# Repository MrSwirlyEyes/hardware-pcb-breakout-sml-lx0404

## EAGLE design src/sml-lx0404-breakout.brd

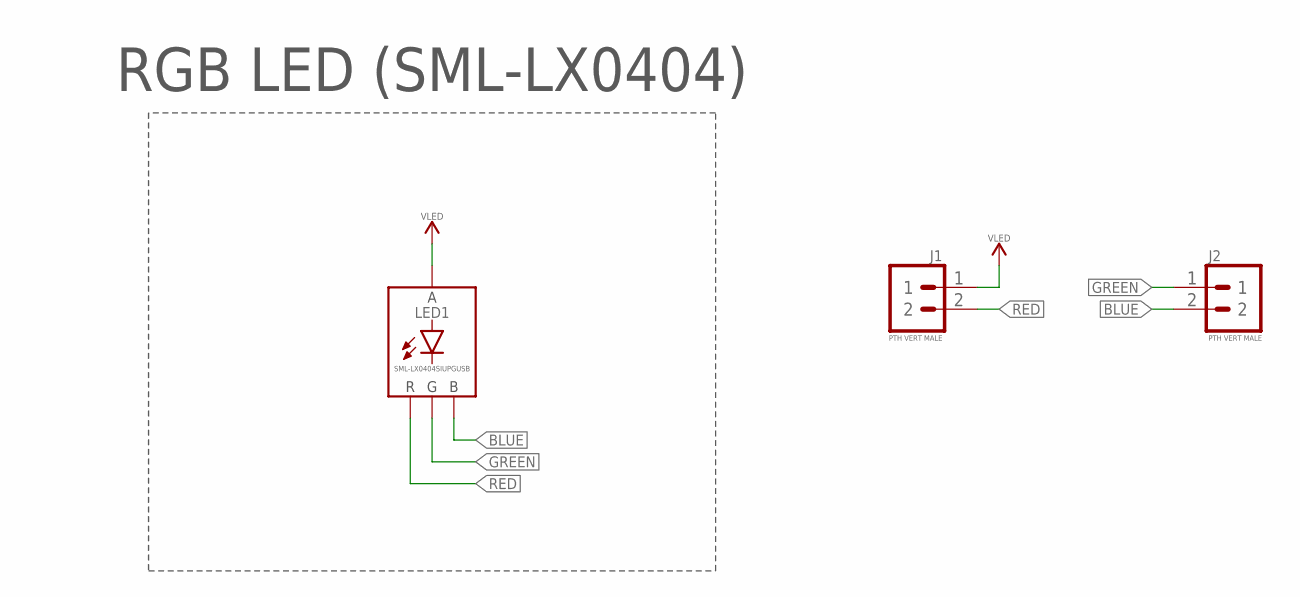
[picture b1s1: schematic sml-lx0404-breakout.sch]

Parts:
J1, J2: PTH VERT MALE; HDRV2W64P254_1X2_508X254X838B
LED1: SML-LX0404SIUPGUSB; DIODFN100X100X30-4N

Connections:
BLUE: J2.2, LED1.3 (B)
GREEN: J2.1, LED1.4 (G)
RED: J1.2, LED1.2 (R)
VLED: J1.1, LED1.1 (A)

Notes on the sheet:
RGB LED (SML-LX0404)

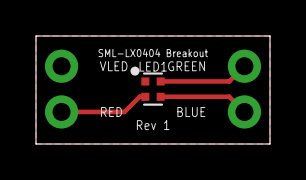
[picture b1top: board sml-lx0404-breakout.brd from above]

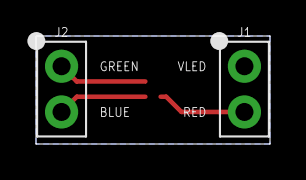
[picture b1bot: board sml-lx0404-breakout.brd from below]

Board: 2 copper layers, 13.0 x 6.0 mm, 3 parts (2 on the bottom side), 4 nets.

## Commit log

2021-01-12 [Rev 1] - Initialize repo.
2021-02-06 Update to fit OSH Park 2-layer board DRU.
2021-08-11 Update CAM files.
